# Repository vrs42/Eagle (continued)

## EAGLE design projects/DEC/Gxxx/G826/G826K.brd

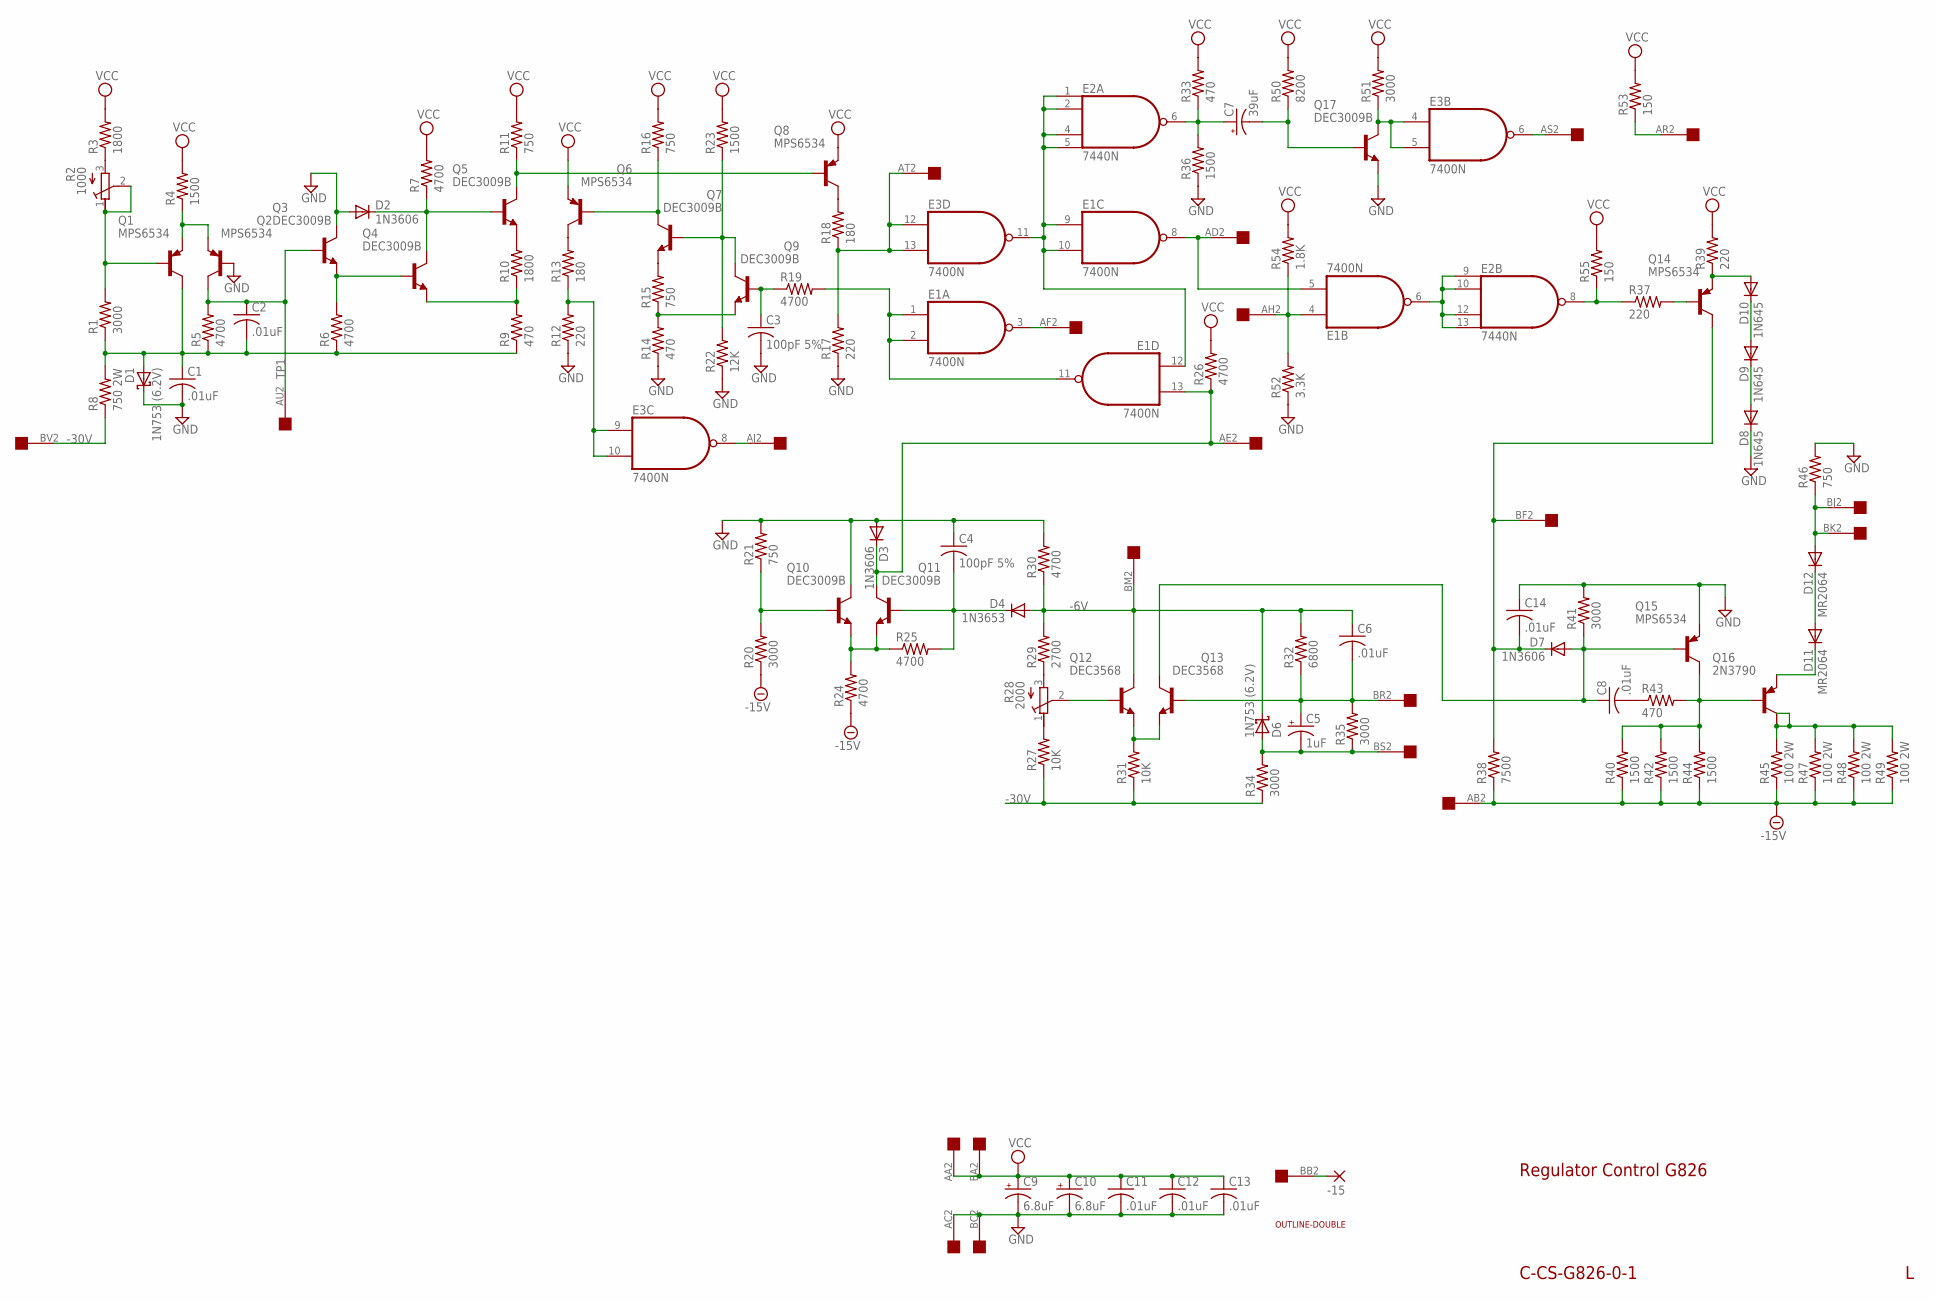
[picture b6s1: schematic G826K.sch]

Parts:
-15: 1,6/0,8
C1, C2, C6, C8, C11, C12, C13, C14: .01uF; C050-025X075
C3, C4: 100pF 5%; C050-025X075
C5: 1uF; E15-5
C7: 39uF; E22-6
C9, C10: 6.8uF; E12-8
D1, D6: 1N753 (6.2V); DO35-10
D2, D3, D7: 1N3606; DO35-10
D4: 1N3653; DO35-10
D8, D9, D10: 1N645; DO35-10
D11, D12: MR2064; DO41-10
E1, E3: 7400N; DIL14
E2: 7440N; DIL14
Q1, Q2, Q6, Q8, Q14, Q15: MPS6534; TO39
Q3, Q4, Q5, Q7, Q9, Q10, Q11, Q17: DEC3009B; TO5
Q12, Q13: DEC3568; TO5
Q16: 2N3790; TO3
R1, R20, R34, R35, R41, R51: 3000; 0207/10
R2: 1000; 3006Y
R3, R10: 1800; 0207/10
R4, R23, R36, R40, R42, R44: 1500; 0207/10
R5, R6, R7, R19, R24, R25, R26, R30: 4700; 0207/10
R8: 750 2W; 0818/25
R9, R14, R33, R43: 470; 0207/10
R11, R15, R16, R21, R46: 750; 0207/10
R12, R17, R37, R39: 220; 0207/10
R13, R18: 180; 0207/10
R22: 12K; 0207/10
R27, R31: 10K; 0207/10
R28: 2000; 3006Y
R29: 2700; 0207/10
R32: 6800; 0207/10
R38: 7500; 0207/10
R45, R47, R48, R49: 100 2W; 0818/25
R50: 8200; 0207/10
R52: 3.3K; 0207/10
R53, R55: 150; 0207/10
R54: 1.8K; 0207/10
U$1: DOUBLE; EDGE-CON4
U$2: OUTLINE-DOUBLE; DOUBLE

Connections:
-6V: C6.1, D4.A, D6.C, Q12.3 (C), R29.2, R30.1, R32.2, U$1.BM2
-15V: R20.1, R24.1, R38.1, R40.1, R42.1, R44.1, R45.1, R47.1, R48.1, R49.1, U$1.AB2
-30V: R8.1, R27.1, R31.1, R34.1, U$1.BV2
GND: C1.2, C3.2, C4.1, C9.-, C10.-, C11.2, C12.2, C13.2, C14.1, D1.C, D2.A, D3.A, D8.C, E1.7 (GND), E2.7 (GND), E3.7 (GND), Q2.2 (B), Q3.3 (C), Q10.3 (C), Q15.1 (E), Q17.1 (E), R12.1, R14.1, R17.1, R21.2, R22.1, R30.2, R36.1, R41.2, R46.2, R52.1, U$1.AC2, U$1.BC2
unnamed: Q1.2 (B), R1.2, R2.1 (A), R2.2 (S)
unnamed: R2.3 (E), R3.1
unnamed: C1.1, C2.2, D1.A, Q1.3 (C), R1.1, R5.1, R6.1, R8.2, R9.1
unnamed: Q1.1 (E), Q2.1 (E), R4.1
unnamed: Q3.1 (E), Q4.2 (B), R6.2
unnamed: Q4.1 (E), R9.2, R10.1
unnamed: D2.C, Q4.3 (C), Q5.2 (B), R7.1
unnamed: Q5.3 (C), Q8.2 (B), R11.1
unnamed: Q5.1 (E), R10.2
unnamed: E3.9 (I0), E3.10 (I1), R12.2, R13.1
unnamed: Q6.3 (C), R13.2
unnamed: E3.8 (O), U$1.AJ2
unnamed: Q6.2 (B), Q7.3 (C), R16.1
unnamed: Q7.1 (E), R15.2
unnamed: Q9.1 (E), R14.2, R15.1
unnamed: Q7.2 (B), Q9.3 (C), R22.2, R23.1
unnamed: Q8.3 (C), R18.2
unnamed: E3.12 (I0), E3.13 (I1), R17.2, R18.1, U$1.AT2
unnamed: E1.9 (I0), E1.10 (I1), E1.12 (I0), E2.1 (I0), E2.2 (I1), E2.4 (I2), E2.5 (I3), E3.11 (O)
unnamed: C3.1, Q9.2 (B), R19.1
unnamed: E1.1 (I0), E1.2 (I1), E1.11 (O), R19.2
unnamed: E1.3 (O), U$1.AF2
unnamed: E1.5 (I1), E1.8 (O), U$1.AD2
unnamed: E1.6 (O), E2.9 (I0), E2.10 (I1), E2.12 (I2), E2.13 (I3)
unnamed: C7.+, E2.6 (O), R33.1, R36.2
unnamed: Q16.C, Q16.C/, R45.2, R47.2, R48.2, R49.2
unnamed: Q15.3 (C), Q16.B, R40.2, R42.2, R43.2, R44.2
unnamed: C7.-, Q17.2 (B), R50.1
unnamed: E3.4 (I0), E3.5 (I1), Q17.3 (C), R51.1
unnamed: E3.6 (O), U$1.AS2
unnamed: E1.4 (I0), R52.2, R54.1, U$1.AH2
unnamed: E2.8 (O), R37.1, R55.1
unnamed: R53.1, U$1.AR2
unnamed: Q14.2 (B), R37.2
unnamed: D10.A, Q14.1 (E), R39.1
unnamed: D8.A, D9.C
unnamed: D9.A, D10.C
unnamed: C14.2, D7.C, Q14.3 (C), R38.2, U$1.BF2
unnamed: -15.1, U$1.BB2
unnamed: Q10.2 (B), R20.2, R21.1
unnamed: Q10.1 (E), Q11.1 (E), R24.2, R25.1
unnamed: D3.C, E1.13 (I1), Q11.3 (C), R26.1, U$1.AE2
unnamed: Q12.2 (B), R28.2 (S)
unnamed: C4.2, D4.C, Q11.2 (B), R25.2
unnamed: Q12.1 (E), Q13.1 (E), R31.2
unnamed: C5.-, D6.A, R34.2, R35.1, U$1.BS2
unnamed: R28.3 (E), R29.1
unnamed: R27.2, R28.1 (A)
unnamed: D11.C, Q16.E
unnamed: C5.+, C6.2, Q13.2 (B), R32.1, R35.2, U$1.BR2
unnamed: C8.1, D7.A, Q13.3 (C), Q15.2 (B), R41.1
unnamed: C8.2, R43.1
unnamed: D11.A, D12.C
unnamed: D12.A, R46.1, U$1.BJ2, U$1.BK2
TP1: C2.1, Q2.3 (C), Q3.2 (B), R5.2, U$1.AU2
VCC: C9.+, C10.+, C11.1, C12.1, C13.1, E1.14 (VCC), E2.14 (VCC), E3.14 (VCC), Q6.1 (E), Q8.1 (E), R3.2, R4.2, R7.2, R11.2, R16.2, R23.2, R26.2, R33.2, R39.2, R50.2, R51.2, R53.2, R54.2, R55.2, U$1.AA2, U$1.BA2

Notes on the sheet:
Regulator Control G826
C-CS-G826-0-1

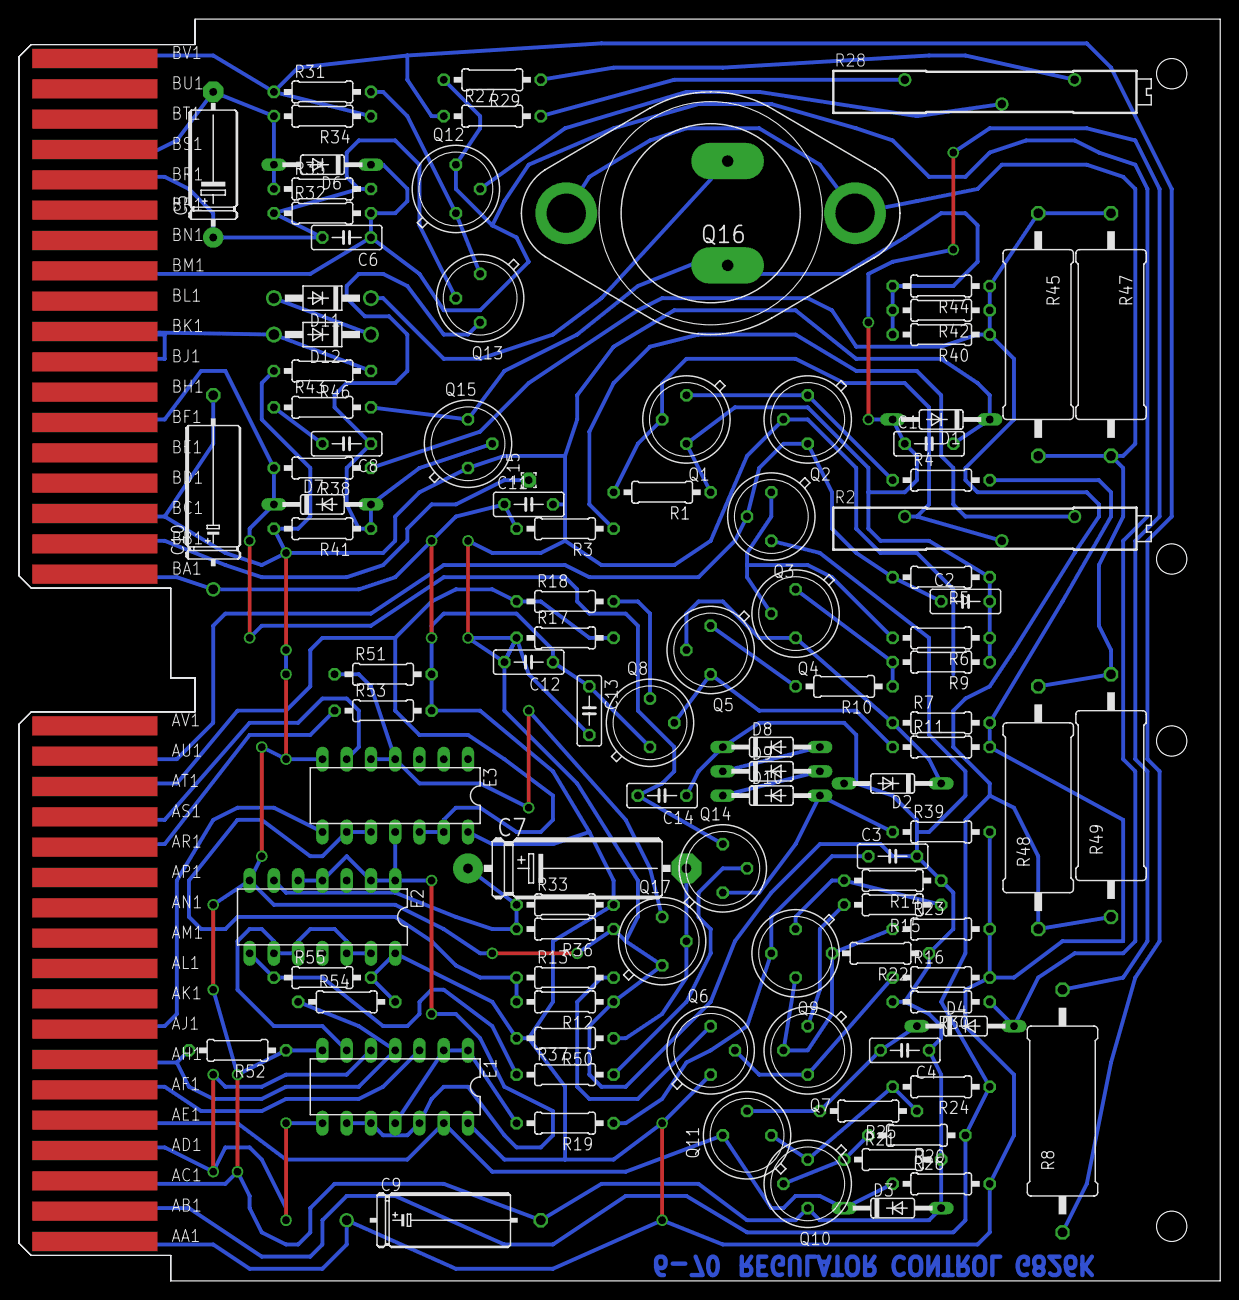
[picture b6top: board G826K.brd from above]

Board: 2 copper layers, 125.7 x 132.1 mm, 103 parts (0 on the bottom side), 60 nets.
